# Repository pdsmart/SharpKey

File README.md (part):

## <font style="color: yellow;" size="6">The SharpKey</font>

<div style="text-align: justify">
The name SharpKey is derived from <b><u>Sharp</u></b> <b><u>Key</u></b>board Interface, as it is based on the original mz25key Sharp MZ-2500/MZ-2800 PS/2 Keyboard Interface.
<div style="padding-top: 0.8em;"></div>
The SharpKey Multi-HID Interface is a device which enables connection of Keyboards and Mice, via PS/2 or Bluetooth, to vintage Sharp and NEC computers. It is
housed in a small KM-24 black or light-grey casing to match the host console colour and takes up minimal additional space. It has two external ports, one for a PS/2 keyboard or mouse and the second
for a cable to connect with the host keyboard or mouse input socket. If bluetooth is used, the PS/2 port is not used and only a host cable from the host port is required.
<div style="padding-top: 0.8em;"></div>
In use the SharpKey takes power from the host, adding little extra overhead to the host computers power supply. It typically consumes a 30mA when active in interface mode rising to 150mA if the IoT web interface is enabled. Peak instantaneous startup current for WiFi can be 250mA.
</div>

<div style="padding-top: 0.8em;"></div>
<div style="text-align: justify">
This section describes the ports, interfaces, buttons and LEDs of the SharpKey.
<div style="padding-top: 0.8em;"></div>
</div>

#### <font style="color: yellow;" size="5">Ports</font>

<div style="text-align: justify">
The SharpKey is equipped with two mini-DIN female ports, an LED and a configuration switch for enabling the on-board WiFi IoT web interface and the Bluetooth device Pairing. The image
below shows the locations.
<div style="padding-top: 0.8em;"></div>
<div style="float: left;">

</div><br>
<div style="padding-top: 0.8em;"></div>
On the left is the HOST connector, this is an 8pin mini-DIN female socket into which a HOST specific cable is plugged. The cable interfaces the SharpKey to either a mouse or keyboard port
on a particular host, ie. Sharp MZ-2800.<br>
<div style="padding-top: 0.8em;"></div>
On the right is the PS/2 connector, this is a 6pin mini-DIN female socket into which a PS/2 keyboard or PS/2 mouse is plugged. This socket is hot-swappable so it is possible to unplug a 
device and re-insert it whilst the interface is powered on. Plugging a different device of the same type is possible but changing from a keyboard to a mouse/vis-a-viz is not possible as it
would require the HOST cable to be changed as well (ie. if the HOST side is connected to the keyboard input of a Sharp X68000 and the PS2 side to a PS/2 Keyboard, you would need to change the HOST
side to a X68000 mouse cable if you wanted to connect a PS/2 Mouse).
<div style="padding-top: 0.8em;"></div>
</div>

<div style='content: ""; clear: both; display: table;'>
    <div style='width: 26%; padding: 5px; padding-left: 1em; float: left'>
        
    </div>
    <div style='width: 25%; padding: 5px; padding-left: 1em; float: left'>
        
    </div>
</div>

<div style="padding-top: 0.8em;"></div>
<div style="text-align: justify">
Internally, there is an 8pin 2mm header connector, this is used when OTA Firmware upgrade fails (ie. bricked) or for development and debugging of new features. See the technical documentation for
more information on this connector and its use.
</div>
<div style="padding-top: 0.8em;"></div>
<div>
    
</div>

#### <font style="color: yellow;" size="5">LEDs</font>

<div style="text-align: justify">
The Blue Activity LED is used to indicate device operation and warn of errors or device status.
<div style="padding-top: 0.8em;"></div>
During normal operation, the Activity LED lights up for a second when the interface is powered on and then the LED powers off. If there is no PS/2 device connected, the LED will light permanently
until a PS/2 device is connected (or Bluetooth enabled and a device pairs with the SharpKey). During keyboard activity, the LED will pulse on each key press. During mouse activity, the LED will
only light up if the 'third wheel button' is pressed and the mouse enters configuration mode.
</div>
<div style="padding-top: 0.8em;"></div>

| LED State           | Occurrence       | Description                    |
| ---------           | -----------      | -----------                    |
| On                  | During power up  | Lights for 1 second then turns off. This indicates normal power up and initialisation successful. |
|                     | Normal use       | PS/2 Keyboard or mouse not connected, Bluetooth device not paired. |
| Off                 | During power up  | Device failure. |
|                     | Normal use       | Device running normally. |
| Pulsing             | Normal use       | LED lights briefly on each keyboard key pressed. |
|                     | WiFi Selection   | LED pulses 1 flash per 0.5 seconds when the WiFi key is being pressed for more than 2 seconds and the SharpKey indicates configured WiFi Client/Access Point mode selected. |
|                     |                  | LED Pulses 1 flash per 0.25 seconds when the WiFi key is being pressed for more than 5 seconds and the SharpKey indicates default parameter Access Point mode selected. |
|                     | Bluetooth Pairing| LED Pulses 1 flash per 0.125 seconds when the WiFi key is being pressed for more than 10 seconds and Bluetooth Pairing mode selected. |
|                     | NVS Reset        | LED Pulses 1 long flash per second when the WiFi key is being pressed for more than 15 seconds and NVS Reset is selected. |

#### <font style="color: yellow;" size="5">Switches</font>

<div style="text-align: justify">
The WiFi/Bluetooth configuration switch is located within the SharpKey casing and accessed via a pin-hole on the casing top, next to the LED. A non-conducting rod needs to be used, inserting
it into the pin-hole and depressing the internal switch.
<div style="padding-top: 0.8em;"></div>
The length of time the switch is depressed indicates the feature the user wishes to access. 
</div>
<div style="padding-top: 0.8em;"></div>

| Time Switch Depressed | LED | Feature |
| --------------------- | --- | ------- |
| 1 second              | Off.                 | Cancel any selected feature, ie. WiFi mode or Bluetooth pairing. |
| 2 key presses in 1 second | SharpKey reboots and LED will light until a key is pressed or mouse moved.                 | Reboot SharpKey. Used if you need to reboot the SharpKey, for example, changing from PS/2 to Bluetooth after disconnecting PS/2 device. |
| 2 - 4 seconds         | Flashes 2 times per second.                 | Select configured WiFi mode, Access Point or Client. |
| 5 - 9 seconds         | Flashes 4 times per second.                 | Select default parameter WiFi Access Point mode. |
| 10 - 14 seconds       | Flashes 8 times per second.                 | Select Bluetooth Pairing mode. |
| 15 - 19 seconds       | Flashes one long pulse per second.          | Select NVS Reset mode (clear all settings and restore to factory mode). |

See the relevant section for more information on accessing and using the different features.

#### <font style="color: yellow;" size="5">Cables</font>

<div style="text-align: justify">
Each host machine has different electrical and mechanical specifications for its keyboard and mouse inputs. The SharpKey is able to manage the electrical and protocol requirements but
the mechanical requirement must be met with a physical cable.
<div style="padding-top: 0.8em;"></div>
This means each host machine keyboard and mouse input port requires a unique cable from the SharpKey into the host keyboard or mouse port. On Sharp machines, the mouse port is common so
only one cable is required to connect the SharpKey to any Sharp mouse port. The different cables can be seen below.
<div style="padding-top: 0.8em;"></div>
</div>

<div style='content: ""; clear: both; display: table;'>
    <div style='width: 40%; padding: 5px; padding-left: 1em; float: left'>
        
    </div>
    <div style='width: 34%; padding: 5px; padding-left: 1em; float: left'>
        
    </div>
</div>
<div style='content: ""; clear: both; display: table;'>
    <div style='width: 23.33%; padding: 5px; padding-left: 1em; float: left'>
        
    </div>
    <div style='width: 33.33%; padding: 5px; padding-left: 1em; float: left'>
        
    </div>
    <div style='width: 33.33%; padding: 5px; padding-left: 1em; float: left'>
        
    </div>
</div>

<div style="text-align: justify">
Each cable has an 8pin mini-DIN connector attached (the MZ-2500 has 2 so either side connector can be used) which plugs into the SharpKey. The opposite end of the cable plugs into the host keyboard or mouse
port.
</div>

#### <font style="color: yellow;" size="5">Connecting the SharpKey</font>

<div style="text-align: justify">
Connecting the SharpKey is simply a matter of obtaining the correct cable for your host machine, either keyboard or mouse, plugging the 8pin mini-din end into the SharpKey and the opposite
end into your host machine keyboard or mouse port. 
<div style="padding-top: 0.8em;"></div>
If you intend to use a PS/2 Keyboard or PS/2 mouse, insert the keyboard/mouse 6pin mini-din connector into the opposite end of the SharpKey. If you are intending to use Bluetooth then no
connection needs to be made with the PS/2 port on the SharpKey.
<div style="padding-top: 0.1em;"></div>
<p style="line-height: 1.2;"><font style="color: silver;" size="4">NB. Bluetooth will only be enabled when no PS/2 device is connected.</font></p>
<div style="padding-top: 0.1em;"></div>
Once the cables have been connected, power on your machine and use the PS/2 keyboard/mouse or Bluetooth keyboard/mouse as normal. If any keyboard keys do no map correctly to the host
keys, you can use the IoT web interface to add key mappings as required.
<div style="padding-top: 0.1em;"></div>
<p style="line-height: 1.2;"><font style="color: silver;" size="4">NB. Bluetooth devices require pairing and once paired, on power up, may take a few seconds to connect. When using Bluetooth at power up, wake the bluetooth devices up by repeatedly hitting the shift key or shaking
the mouse, this is necessary as the device will be in sleep mode and the SharpKey wont be able to connect.</font></p>
</div>

#### <font style="color: yellow;" size="5">Bluetooth Pairing</font>

<div style="text-align: justify">
In addition to PS/2 HID devices, Bluetooth wireless devices can also be connected to the SharpKey.
<div style="padding-top: 0.8em;"></div>
In order to use Bluetooth, <u>No</u> PS/2 device should be connected to the SharpKey. If the SharpKey detects a PS/2 device during startup it will not enable Bluetooth.  The Bluetooth transceiver in the ESP32 is
not so powerful so your device needs to be in a 1m range or less (some devices, typically mice, operate over a much longer distance). 
<div style="padding-top: 0.8em;"></div>
On receipt, in <i>factory default mode</i> or after an <i>NVS Clear</i> function, the SharpKey will perform a Bluetooth scan looking for nearby devices which are in Pair mode. Simply press the <i>pairing</i> button on your keyboard or mouse device and within 5-10 seconds it should connect
without requiring a pairing PIN.
<div style="padding-top: 0.8em;"></div>
Upto 5 additional devices can be paired with the SharpKey (which will operate simultaneously if all 5 devices are connected) can be added by placing the SharpKey into <i>Pairing Mode</i>. To enter <i>Pairing Mode</i> press the Wifi/Config Enable switch for 10-15 seconds, as you hold the key
you will notice the Blue LED change pattern:
<ul style="line-height: 0.6em;"><font size="3">
<li>2-5 seconds it will flash twice per second which indicates <i>WiFi Enable Mode</i> is selected if you release the switch.</li>
<li>5-10 seconds it will flash 4 time per second indicating <i>Default WiFi Mode</i> is selected if you release the switch.</li>
<li>10-15 seconds it will flash 8 times per second indicating <i>Bluetooth Pairing Mode</i> selected if you release the switch.</li>
</font></ul>

Release the switch after 10 seconds and the SharpKey will enter pairing mode and connect with any HID devices it finds in Pairing mode. The SharpKey stays in 
pairing mode for 60 seconds during which time it will pair with as many HID devices it finds.
<div style="padding-top: 0.8em;"></div>
Device authentication (PIN entry) has been programmatically disabled for the SharpKey as it has no means to display a pairing PIN. This method generally works well for most BLE and BT Classic devices
but should your device require a PIN which cannot be disabled, after about 10 seconds the Blue LED will start flashing with 3 long pulses, repeated every second. If you see the LED flashing then enter the PIN code '<u>1234</u>' on your keyboard and press ENTER. If the LED continues
to flash, repeat the PIN entry until it pairs and the LED stops flashing.
<div style="padding-top: 0.8em;"></div>
On future power cycles of the SharpKey it will be necessary to shake or wake your bluetooth device so that it reconnects. This can be achieved by pressing the <i>Shift</i> key repeatedly on your keyboard or moving your mouse. If the bluetooth devices isnt woken, the SharpKey wont be able to see
it and connect. It can take 1-10 seconds to reconnect depending on your device and range from the SharpKey (the further the distance the longer it may take due to the ESP32 Bluetooth transceiver not being very powerful).
</div>

#### <font style="color: yellow;" size="5">Accessing the IoT Web Interface</font>

<div style="text-align: justify">
The SharpKey has several preconfigured keyboard maps, factory default set to a UK keyboard layout on all of the supported host machines. Using hotkeys (see below) it is possible to select a different map.
<div style="padding-top: 0.8em;"></div>
The in-built maps will evolve over time to support more keyboards and these updates will be distributed as a firmware update. Keyboards layouts currently supported are:
<ul style="line-height: 0.6em;"><font size="3">
  <li>Wyse KB-3926 UK Layout</li>
  <li>Generic OADG109 Japanese Layout</li>
  <li>Sanwa SKB-L1 Japanese Layout</li>
  <li>Perixx Periboard 810 UK Layout</li>
  <li>OMOTON K8508 UK Layout</li>
</font></ul>

There exists however an edge case of a key not working or not working the way it should for
an individual user, also other users may find their regional (country) keyboards not working well and these shortcomings needs to be addressed by the user who has more hands on experience.
To this end, the SharpKey can be configured to map any PS/2 code or code combinations into a key sequence expected by the active host. Bluetooth scancodes are internally mapped to PS/2 scancodes 
so all keyboard type (PS/2 or Bluetooth) mapping is performed using PS/2 codes.
<div style="padding-top: 0.8em;"></div>
In order to make changes the SharpKey is equipped with an in-built web server using WiFi technology and can be configured in Access Point mode (you connect your WiFi device to the SharpKey) or Client mode
where the SharpKey uses stored credentials to connect with your home network router.
<div style="padding-top: 0.8em;"></div>
To access the web interface, the SharpKey needs to enable the wifi Access Point or Client transceiver. This is done via the <a href="/sharpkey-usermanual/#switches">WiFi/BT Config switch</a>.
<div style="padding-top: 0.8em;"></div>
There are two WiFi modes, Access Point and Client:
<ul>
<li>Access Point is where the SharpKey acts as a WiFi router and you search via your computer/phone wifi settings for the WiFi network:
<font style="color: Tan;">sharpkey</font> and connect using the password: <font style="color: Tan;">sharpkey</font>. The SSID and password can be changed in the configuration but should you forget your changes, pressing the  WiFi/BT switch for more than 5 seconds
will force the SharpKey to enter Access Point mode using the aforementioned defaults.</li>
<li>Client mode is where the SharpKey connects to your home network, details of which must be pre-entered into the SharpKey via the Access Point mode. Once set, each time the SharpKey enters WiFi mode
it will automatically try to connect to your router, using DHCP (your router allocates it an address) or with a fixed address you provide.</li>
</ul>

The steps for accessing each of the modes can be seen in the table below.
<div style="padding-top: 0.8em;"></div>
</div>

| Mode                        | How to Access | Description                                |
| ----                        | ------------- | -----------                                |
| Access Point mode.<br>Initial setup or by forcing default mode. | Initial factory setup, pressing the WiFi switch for 5-10 seconds will enter WiFi Access Point mode. If a bad configuration has been made or you have a network change, press the WiFi switch for 5-10 seconds to load default parameters and enter Access Point mode. | Search on your computer or phone WiFi settings menu for the network:<font style="color: Tan;">sharpkey</font>. Connect with this network and enter the password:<font style="color: Tan;">sharpkey</font>. After successful connection, open a web browser and enter in the address bar: http://192.168.4.1 - you will now be able to access the SharpKey and configure the WiFi via <font style="color: Tan;">WiFi Manager</font>.|
| Access Point mode.          | Once the SharpKey has been configured and you selected AP Mode in the WiFi Manager, pressing the WiFi switch for 2-5 seconds will enter Access Point mode. | This mode is where you have selected Access Point mode via the WiFi Manager menu in the browser configuration. You can change the network name (SSID), password and IP address range to suit your requirements. In this mode you will always connect to the SharpKey by joining its network in the WiFi settings menu of your computer or phone and access the configuration web page using the settings you provided. |
| Client (also called Station) mode. | Once the SharpKey has been configured and you selected Client Mode in the WiFi Manager, pressing the WiFi switch for 2-5 seconds will enter Client mode. | This mode allows the SharpKey to connect with your network via WiFi login to your router. During the initial connection in Access Point mode, under the WiFi Manager menu, select and setup Client mode with your router credentials. Once configured, everytime you enable WiFi the SharpKey will connect to your router and be accessible by an allocated IP address on your network or a fixed IP address you entered in the WiFi Manager menu. |

<div style="text-align: justify">
After pressing the WiFi configuration switch for the required amount of time the device will reboot and enter the requested WiFi mode. The blue led will light and if it remains lit then an error has occurred. If it briefly flashes several times then the desired WiFi configuration has been setup and established.
<div style="padding-top: 0.8em;"></div>
If all is successful and you have either joined the Access Point network or the SharpKey has connected to your network, opening a browser and entering the correct IP address, (ie. http://192.168.4.1 for the initial Access Point mode) will see the status screen below.
The correct IP address is the one you configured in WiFi Manager, or in the case of Client Mode with DHCP enabled, the one allocated by your router which you can find by looking at the admin page of your router.
<div style="padding-top: 0.8em;"></div>
A visual indication of the SharpKey connecting to your
</div>

<div style="padding-top: 0.8em;"></div>

#### <font style="color: yellow;" size="5">Configuring Access Point Mode</font>

<div style="text-align: justify">
The SharpKey factory state automatically starts in Access Point mode when WiFi is enabled. WiFi is enabled by pressing the WiFi/BT Config switch for 2-5 seconds. Once the device is configured, if the device cannot be accessed (for example, due to network change), pressing the WiFi/BT Config switch for 5-10 seconds will automatically enter Access Point mode with default parameters.
<div style="padding-top: 0.8em;"></div>
The default parameters in unconfigured Access Point mode are below.
</div>
<div style="padding-top: 0.8em;"></div>

| Parameter      | Value |
| ---------      | ----- |
| SSID (network name) | sharpkey |
| Password       | sharpkey |
| Access Point IP address | 192.168.4.1 |
| Router address | 192.168.4.1 |
| DHCP assigned IP range | 192.168.4.2 - 192.168.4.254 |

<div style="text-align: justify">
After setting the SharpKey into WiFi mode, access the WiFi menu of your computer or phone and select the <font style="color: Tan;">sharpkey</font> network. Enter the password <font style="color: Tan;">sharpkey</font>, your computer or phone will now join the SharpKey network and you can access it's web interface.
<div style="padding-top: 0.8em;"></div>
Enter the URL http://192.168.4.1 into a web browser and you will be presented with the status screen:
</div>

<div style="text-align: justify">
The status screen shows 2 panels, a <font style="color: Tan;">WiFi Configuration</font> panel which shows the active WiFi configuration being used by the SharpKey and a <font style="color: Tan;">Version Information</font> panel which shows the firmware modules installed along with their version number and the disk filesystem version. This information can be used
for feature verification or fault tracking/raising a support ticket and also to view versions to see if an update pack offers newer software or fixes.
<div style="padding-top: 0.8em;"></div>
In the left side of the screen, called the sidebar menu, are the possible options available to view or configure in the web interface. This document details each of the options in more detail further down.
<div style="padding-top: 0.8em;"></div>
Click on the <font style="color: Tan;">WiFi Manager</font> option in the left sidebar menu. This will start the WiFi Manager configuration screen which will appear like:
</div>

<div style="text-align: justify">
You now have a choice, configure the SharpKey as an Access Point or as a Client. Access Point means the SharpKey provides the WiFi network and your computer/phone needs to connect with it via the WiFi settings menu. Client mode means you enter details of your home network and the SharpKey will automatically connect to your home network and your computer or phone
will see it as a device on your network.

If you decide to use Access Point mode, you can leave it configured with the defaults, or change them with the <i>Configure WiFi</i> panel below.
</div>

<div style="text-align: justify">
The options for the Access Point mode in the <i>Configure WiFi</i> panel are:
</div>
<div style="padding-top: 0.8em;"></div>

| Option    | Description |
| ------    | ----------- |
| WiFi Mode | Select the type of mode required, in this instance click on <font style="color: Tan;">Access Point</font>. |
| SSID      | This is the network name you will see on your computer or phone when you go to the Wifi settings menu and scan for available networks. Either leave it as default or change to a meaningful name. |
| Password  | This is the password your computer or phone will request when you choose to join the network identified by SSID. |
| IP Address| This is the IP address range the SharpKey will use for its DHCP server which allocates any connecting clients requesting an address. This value should end with a .1 which is assigned to the SharpKey and the DHCP server will allocate addresses xxx.xxx.xxx.2 - 254 to a connecting client. |
| Netmask   | This is the network mask used for filtering and masking IP addresses. Unless you are network savvy, always set this address to 255.255.255.0. |
| Gateway   | This is the gateway a computer or phone needs to route network requests. This should be the same as IP Address as the SharpKey doesnt perform routing. |

<div style="text-align: justify">
Once you have entered the required settings, press on <font style="color: Wheat;">Save</font> and the data will be validated. If the data is correct, a message will be displayed in green advising you all is ok and to press Reboot. If the message is in red, take note of the error and correct accordingly, pressing <font style="color: Wheat;">Save</font> once the error has been fixed.
<div style="padding-top: 0.8em;"></div>
After a successful save, press reboot and the SharpKey will reboot,  immediately entering WiFi mode for data confirmation (ie. you dont need to press the WiFi/BT Config switch again). Just allow a few seconds and then join with the SharpKey network using your computer or phones WiFi settings menu. Once connected to the SharpKey network, open a browser and enter the IP Address you 
chose in the <i>Configure WiFi</i> panel and you will be immediately taken to the SharpKey status menu.
</div>

#### <font style="color: yellow;" size="5">Configuring Client Mode</font>

<div style="text-align: justify">
The SharpKey factory state automatically starts in Access Point mode when WiFi is enabled. Follow the Access Point mode configuration up until you see the SharpKey status screen and follow the instructions below.
</div>

<div style="text-align: justify">
Click on the 'WiFi Manager' option in the left sidebar menu. This will start the WiFi Manager configuration screen which will appear like:
</div>

<div style="text-align: justify">
You now have a choice, configure the SharpKey as an Access Point, in which case follow the <font style="color: Tan;">Configure Access Point Mode</font> instructions, or configure the SharpKey in Client Mode.
<div style="padding-top: 0.8em;"></div>
If you decide on Client Mode, click on the <font style="color: Tan;">Client</font> radio button and the <i>Configure WiFi</i> panel will update to request Client parameters. There are two distinct Client mode's of operation, either <font style="color: Tan;">DHCP Enabled</font> where the router provides all network connection information or <font style="color: Tan;">DHCP Disabled</font> where you manually specify network parameters.
<div style="padding-top: 0.8em;"></div>
The initial parameters requested in the <i>Configure WiFi</i> panel appear below, which is the same for DHCP Enabled or Disabled mode.
</div>
<div style="padding-top: 0.8em;"></div>

| Option    | Description |
| ------    | ----------- |
| WiFi Mode | Select the type of mode required, in this instance click on <font style="color: Tan;">Client</font>. |
| SSID      | This is the network name you want the SharpKey to join with in order to establish a connection with your home network. |
| Password  | This is the password the SharpKey will provide to your router to authenticate itself and establish a connection. |
| DHCP Mode | This specifies wether you want your router to provide all network information (Enabled) or you will manually provide it (Disabled). |

The panel will appear as indicated below:

<div style="text-align: justify">
Should you decide to use DHCP Disabled mode, additional parameters are requested in the <i>Configure WiFi</i> panel:
</div>
<div style="padding-top: 0.8em;"></div>

| Option    | Description |
| ------    | ----------- |
| IP Address| This is the address the SharpKey will use for itself on your home network. You will connect to the SharpKey using this address in your browser, ie. http://&lt;IP Address&gt;. |
| Netmask   | This is the filter and masking parameter in order for your SharpKey to occupy parts of a subnet. Unless your network savvy, enter 255.255.255.0 |
| Gateway   | This is the IP address of the device on your network which acts as a gateway to the internet/intranet. The SharpKey is not internet aware so enter the same value as the IP Address above. |

The updated panel will appear as indicated below:

<div style="text-align: justify">
Once you have set the correct mode of operation and entered the requested parameters press <font style="color: Wheat;">Save</font> and the parameters will be validated and updated. Should the parameters be valid a green success message will appear indicating this and requesting you to press reboot. Should the parameters be invalid, a red message will appear indicating which entry is incorrect, fix it and press <font style="color: Wheat;">Save</font> again.
<div style="padding-top: 0.8em;"></div>
After a successful save, press <font style="color: Wheat;">Reboot</font> on the left side-bar and the SharpKey will reboot. Press the WiFi switch again if you want to enter WiFi mode with the new settings. If the SharpKey fails to join with the network the LED will stay lit otherwise will blink several short pulses to confirm WiFi connection. If the SharpKey fails to enter WiFi mode (ie. cannot connect with your router), the LED will remain lit and after 1 minute
it will reboot. In this situation, press the WiFi/BT Config switch for 5-8 seconds and it will enter WiFi Access Point mode with default settings so you can reconfirm the credentials you entered.
</div>

#### <font style="color: yellow;" size="6">OTA Updates</font>

<div style="text-align: justify">
The SharpKey is equipped with a feature to allow updates to its internal firmware or disk filing system. The firmware or filesystem can be upgraded for newer features or to fix known bugs. 
<div style="padding-top: 0.8em;"></div>
In order to use the OTA Updates feature, access the web interface using the Access Point/Client information above and open a browser to load the initial status page, ie:
</div>

<div style="text-align: justify">
Click on the <font style="color: Tan;">OTA Update</font> option in the left sidebar menu. This will start the OTA Update configuration screen which will appear like:
</div>

<div style="text-align: justify">
The OTA Update screen shows 4 panels:
   
<ul>
 <li>a <font style="color: Tan;">Version Information</font> panel which shows the firmware modules installed along with their version number and the disk filesystem version. This information can be used
for feature verification or fault tracking/raising a support ticket and also to view versions to see if an update pack offers newer software or fixes.</li>
<li>an <font style="color: Tan;">ESP32 Partitions</font> panel which shows the layout of the NVS Flash RAM on the ESP32 SoC which powers the SharpKey. The information of interest is the Partion Names: ota_0, ota_1 and filesys. The SharpKey uses a fault tolerant update system in a round robin method. If the current firmware is running on partition ota_0 then any updates will be placed onto ota_1. After update, should
the SharpKey fail to boot an automatic rollback is performed and the SharpKey will reboot off ota_0. This is not the case for the filesystem <font style="color: Tan;">filesys</font>, if an update fails then the filesystem may be corrupted and the web interface will fail to work. In this case an external programming probe needs to be connected to the SharpKey in order to reflash the filesystem. This is a rare occurrence and
only happens due to software bugs or power outages.</li>
<li>a <font style="color: Tan;">Firmware Upload</font> panel which allows you to select a new firmware file and upload it into the SharpKey.</li>
<li>a <font style="color: Tan;">File Pack Upload</font> panel which allows you to select a new filesystem image file and upload it into the SharpKey.</li>
</ul>

In order to upgrade the firmware, click on the <font style="color: Wheat;">Select file</font> button in the <font style="color: Tan;">Firmware Upload</font> panel and choose a stored or downloaded firmware image. Validation will occur before programming so if you choose the wrong image, the SharpKey will refuse to update. Validation will also check the version and block the update if the version chosen is the same as the current firmware. Once selected, the panel will update as follows:
</div>

<div style="text-align: justify">
Click on the <font style="color: Wheat;">Upgrade</font> button if you are ready to upload and flash the new firmware into the SharpKey or click <font style="color: Wheat;">Cancel</font> to clear the chosen file. Once you press <font style="color: Wheat;">Upgrade</font> the update procedure will commence, firstly the file will be validated and if valid, file upload will take place and the panel will change showing the status:
</div>

<div style="text-align: justify">
After a successful upload, a green success message will appear advising you to perform a reboot operation. If a red message appears, reboot the SharpKey and try the firmware upload again. The failsafe mechanism will never overwrite the current firmware so you can always restart the SharpKey.
</div>

<div style="text-align: justify">
In order to upgrade the filepack (the filesystem which contains key mapping images and web server files), click on the <font style="color: Wheat;">Select file</font> button in the <font style="color: Tan;">File Pack Upload</font> panel and choose a stored or downloaded filepack image. Validation will occur before programming so if you choose the wrong image, the SharpKey will refuse to update. Once selected, the panel will update as follows:
</div>

<div style="text-align: justify">
Click on the <font style="color: Wheat;">Upgrade</font> button if you are ready to upload and flash the new filepack into the SharpKey or click <font style="color: Wheat;">Cancel</font> to clear the chosen file. Once you press Upgrade the update procedure will commence, firstly the file will be validated and if valid, file upload will take place and the panel will change showing the status:
</div>

<div style="text-align: justify">
After a successful upload, a green success message will appear advising you to perform a reboot operation.
<div style="padding-top: 0.8em;"></div>
If a red message appears, reboot the SharpKey and try the filepack upload again. In this situation, where a filepack update has failed, if the SharpKey fails to enter WiFi mode then there is a good chance the filesystem is corrupted. The SharpKey interface will continue
to operate but no access will be possible to the web interface. In order to correct this, an external programming probe needs to be connected to the SharpKey in order to reflash the filesystem. See the technical documentation on a correct procedure. The situation where a filepack upload fails and corruption occurs should be very rare, just ensure power is continuously applied
to the SharpKey during an upload.
</div>

## <font style="color: yellow;" size="6">Key Map Editor</font>

<div style="text-align: justify">
To cater for unmapped key combinations or keyboards with different layout, configuration and scan codes, the SharpKey allows keyboard map editting. The key maps can be updated via the in-built keymap editor or via a local file save-edit-upload procedure using a tool such as <font style="color: Tan;">dhex</font>. If the key mapping file becomes corrupted you can upload a backup from local file or
let the SharpKey reload from the internal default map so another attempt at key map editting can be made.
<div style="padding-top: 0.8em;"></div>
Given the differences between the various supported machines, the key map editor and it's data differ per model, so a section is dedicated to each machine below, describing the mapping logic and the editor use in making changes. The keymap can only be editted for the active host detected by the SharpKey on startup. If a host is not detected then no keymap editting option will 
appear in the left side bar menu.
<div style="padding-top: 0.8em;"></div>
The basic key map editor, common to all supported hosts, is based on a hex input table, with mapping priority top down, where each entry in the table specifies one key map. Data can be entered in hex or decimal values and some input fields have popover boxes which aid in choosing features such as SHIFT key to aid in the configuration process. 
<div style="padding-top: 0.8em;"></div>
To access the keymap editor of the active host, start the web interface using the Access Point/Client information above and open a browser to load the initial status page, an example of which is below.
</div>

<div style="text-align: justify">
Click on the <font style="color: Wheat;">&lt;HOST&gt; KeyMap</font> option in the left sidebar menu. This will start the key map editor screen for the active host which will be similar to the example below.
</div>

<div style="text-align: justify">
There are 2 panels in the keymap editor, one is for direct input and editting of the key map values, the second is for saving and loading of a keymap file to a local disk. The latter option can be used for backup or to allow external editting of the keymap using local computer tools.
<div style="padding-top: 0.8em;"></div>
In the <font style="color: Tan;">KeyMap Editor</font> panel, a table will be displayed, based on responsive technology which will auto size to the viewable window, use the mouse scroll wheel to scroll down or the TAB/Cursor keys to scroll left and right.
<div style="padding-top: 0.8em;"></div>
The table headers differ depending on the active host and will be described in more detail in the host sections below.
<div style="padding-top: 0.8em;"></div>
The editor can add, delete, swap, save changes or reload using the four buttons amd two columns on the right of the table as follows: 
<ul>
<li>to add a column, click the green + symbol and a blank line will appear on the row below the +. All values will be set to disabled and require completion to become active.</li>
<li>to delete a single row, click the red - symbol ON the row you wish to delete.</li>
<li>to delete multiple rows, click on the Tick Box to the right of each row to be deleted. When one or more tick boxes are ticked, the blue <font style="color: Wheat;">Delete</font> button will be made active, press <font style="color: Wheat;">Delete</font> and the rows will be removed.</li>
<li>to swap TWO rows, click the Tick Box to the right of each row, TWO rows only should be ticked. Once two rows have been ticked, the blue <font style="color: Wheat;">Swap</font> button will be made active, press <font style="color: Wheat;">Swap</font> and the rows will be swapped.</li>
<li>to save the keymap (make it active on next reboot), once you have made data changes the blue <font style="color: Wheat;">Save</font> button will be made active, click on it to save the changes.</li>
<li>once changes have been made, the blue <font style="color: Wheat;">Reload</font> button will be made active, clicking this button at any time will discard all changes and reload the keymap.</li>
</ul>

Messages will be displayed in the status box just above the buttons, this is where errors will be reported if any occur.
<div style="padding-top: 0.8em;"></div>
Please see the sections below for more specific keymap detail.
</div>

#### <font style="color: yellow;" size="5">Sharp MZ-2500 / MZ-2800 Key Map</font>

<div style="text-align: justify">
The MZ-2500 and MZ-2800 models share a common key map table. In common with other supported host machines, the key map allows targetting a map at a specific keyboard model (ie. Wyse KB-3296) and a specific host variant (ie. MZ-80B on an MZ-2500). 
<div style="padding-top: 0.8em;"></div>
The MZ-2500/MZ-2800 machines use a keyboard which is based on a 13x8 or 14x8 key matrix where all inactive keys see a logic <font style="color: Tan;">1</font> and an active key sees a logic <font style="color: Tan;">0</font>. The MZ-2500 keyboard matrix can be visualised in the following tables and image along with the keyboard layout. The first table has the column as the horizontal header and the second table has the row as the horizontal header.
</div>
        
        MZ-2500 Keyboard Map.
        
         Row     D7        D6        D5        D4        D3        D2        D1        D0
        ----------------------------------------------------------------------------------
          0      F8        F7        F6        F5        F4        F3        F2        F1
          1      KP -      KP +      KP .      KP ,      KP 9      KP 8      F1O       F9
          2      KP 7      KP 6      KP 5      KP 4      KP 3      KP 2      KP 1      KP 0
          3      BREAK     RIGHT     LEFT      DOWN      UP        RETURN    SPACE     TAB
          4       G         F         E        D         C         B         A         / ?
          5       O         N         M        L         K         J         I         H
          6       W         V         U        T         S         R         Q         P
          7       , <       . >       _        YEN |     ^ '¿      Z ¿       Y         X ¿ 
          8       7 '       6 &       5 %      4 $       3 #       2 "       1 !       0
          9                 [ {       @ `      - =       ; +       : *       9 )       8 (
         10       KP /      KP *      ESC      BACKSPACE INST/DEL  CLR/HOME  COPY      ] }
         11                                    CTRL      KANA      SHIFT     LOCK      GRAPH
         12                                                                  KJ2       KJ1 
         13                                                                  HELP      ARGO 
        
         Col      0        1         2         3         4         5         6         7        8        9        10       11       12      13
         --------------------------------------------------------------------------------------------------------------------------------------
         D0       F1       F9        KP 0      TAB       / ?       H         P         X        0        8 (      ] }      GRAPH    KJ1     ARGO
         D1       F2       F10       KP 1      SPACE     A         I         Q         Y        1 !      9 )      COPY     LOCK     KJ2     HELP
         D2       F3       KP 8      KP 2      RETURN    B         J         R         Z        2 "      : *      CLR/HOME SHIFT
         D3       F4       KP 9      KP 3      UP        C         K         S         ^ '¿     3 #      ; +      INST/DEL KANA
         D4       F5       KP ,      KP 4      DOWN      D         L         T         YEN |    4 $      - =      BACKSPACE CTRL
         D5       F6       KP .      KP 5      LEFT      E         M         U         _        5 %      @ `      ESC
         D6       F7       KP +      KP 6      RIGHT     F         N         V         . >      6 &      [ {      KP *
         D7       F8       KP -      KP 7      BREAK     G         O         W         , <      7 '               KP /

<div style="text-align: justify">
The MZ-2800 keyboard matrix can be visualised in the following images, the first image is the keyboard layout and the second is the keyboard matrix.
</div>

<div style="text-align: justify">
A PS/2 key (Bluetooth keyboards are internally mapped to PS/2 keys) may require activation of one or more row/column pairs within the keyboard matrix AND possibly deactivation of another row/column pair. To cater for this, 14 parameters are
provided per single key map, all of which need to be configured or defaulted, which is described below.
<div style="padding-top: 0.8em;"></div>
The mapping process traverses the mapping table from top to bottom everytime a PS/2 key is pressed and if a key is matched, the MZ-2500/2800 output matrix is updated using a <font style="color: Tan;">Make Row</font> parameter which points to a row in the matrix and a <font style="color: Tan;">Make Key</font> parameter which sets, via logical OR, the 8 bit column data for that row. 
Upto 3 matrix bits can be set (3 key presses on the MZ-2500/2800 keyboard) per PS/2 key. Upto 2 matrix releases can be set per PS/2 key. A key release is used when a modifier may already have been pressed, ie. SHIFT and it needs to be released to set the required key into the matrix. Both set and releases use logic <font style="color: Tan;">1</font> to indicate an active state.
<div style="padding-top: 0.2em;"></div>
<p style="margin-left:2%; margin-right: 1%;"><font size="4">ie. Make Row 1 = 0x01, Make Key 1 = 0x80 - Using the MZ-2500 matrix map below, this combination would see the KeyPad Minus key being pressed on the output matrix which is sent to the MZ-2500 as keyboard input, the MZ-2500 would then react by detecting and acting on a KeyPad Minus key being pressed.</font></p>
<div style="padding-top: 0.2em;"></div>
In the mapping table, for the matrix Row and Key values, a set bit = 1 and a reset bit = 0 which is the inverse of the actual MZ-2500/MZ-2800 keyboard matrix state but makes understanding and configuration easier. If the Row is set to 255 (0xFF), which is a marker value indicating an unused parameter, then that particular entry is ignored. 
<div style="padding-top: 0.8em;"></div>
The following table describes each configurable parameter forming a single key map.
</div>
<div style="padding-top: 0.8em;"></div>

| Parameter        | Description |
| ---------        | ----------- |
| PS/2 KeyCode     | This is the raw PS/2 Keyboard Code for any given key excluding E0/E1 or Break modifiers which are reflected in the PS/2 Control Key flag. |
| PS/2 Control Key | This is the control keys to be matched for any given PS/2 KeyCode. They include SHIFT, CTRL, CAPS, ALT, ALTGR, GUI, FUNC and BREAK (not break key but key break or release). |
| For Keyboard     | This is a flag to specify a particular PS/2 or Bluetooth keyboard model(s) to which this map will be active if the connected keyboard matches. |                                                              
| For Host Model   | This is a flag to specify a model or set of models the key map is active for. The MZ-2500 can emulate an MZ-80B, MZ-2000 and MZ-2500 and the MZ-2800 can emulate an MZ-2500 or MZ-2800. |                                                            
| Make Row 1       | This is the row in the MZ-2500/MZ-2800 keyboard matrix to activate when the defined PS/2 KeyCode matches. |                                                           
| Make Key 1       | This is the column in the MZ-2500/MZ-2800 keyboard matrix which will be activated for a matching PS/2 KeyCode. |                                                           
| Make Row 2       | Same as Make Row 1, second row activation if required. 0xFF = disabled. |                                                          
| Make Key 2       | Same as Make Key 1.            |                                             
| Make Row 3       | Same as Make Row 1, third row activation if required. 0xFF = disabled. |                                                        
| Make Key 3       | Same as Make Key 1.           |                                            
| Break Row 1      | This is the row in the MZ-2500/MZ-2800 keyboard matrix to be de-activated, if set, when the defined PS/2 KeyCode matches. |
| Break Key 1      | This is the column in the MZ-2500/MZ-2800 keyboard matrix which will be de-activated when PS/2 KeyCode matches. |
| Break Row 2      | Same as Break Row 1, second row to be de-activeted if required. oxFF = disabled. |
| Break Key 2      | Same as Break Key 1.   |

<div style="text-align: justify">
All the keymap parameters are shown in the key map editor using HEX notation, ie:
</div>

<div style="text-align: justify">
All the keymap rows are stored in the table and the viewable table size is set according to the browser and/or computer screen size. To view hidden rows, use the mouse scroll wheel.
<div style="padding-top: 0.8em;"></div>
Data entry can be made in HEX or DECIMAL notation by clicking on a column and entering a value, then click on the next column and enter a value repeating, or click once then use the TAB key for more rapid data entry. Detail for each column
and it's reqired input values can be seen below.
<div style="padding-top: 0.8em;"></div>
<font style="color: cyan;">PS/2 KeyCode</font> - This column expects a PS/2 or Bluetooth keyboard scancode which can be found in your keyboard user manual or on the web where there are many references.
ie. the key <font style="color: Tan;">A</font> has a generic scancode value of 0x1C. HEX codes are not that user friendly and as there are many keyboards with many differing scancodes it is not possible to offer a picklist.
<div style="padding-top: 0.8em;"></div>
PS/2 scancodes can be represented by multiple bytes, only use the primary byte and ignore extended code seqeuences such as E0/E1/F0 as these are internally processed and the corresponding feature selected in the <font style="color: Tan;">PS/2 Control Key</font> column.
<div style="padding-top: 0.8em;"></div>
<font style="color: cyan;">PS/2 Control Key</font> - This parameter indicates which modifier keys (ie. CTRL, SHIFT etc) are pressed along with the PS/2 scancode in order to make a match. As a hex value is required, the modifier values are as follows:
</div>
<div style="font-size: 20px; border-collapse: collapse; table-layout: fixed; border: 3px;margin: 0;padding:0.2em;">
<table>
<tr>
  <th>Modifier Key</th><th>Value</th> <th>Modifier Key</th><th>Value</th> <th>Modifier Key</th><th>Value</th> <th>Modifier Key</th><th>Value</th>
</tr>
<tr>
  <td>SHIFT</td><td>0x01</td><td>CTRL</td><td>0x02</td><td>CAPS</td><td>0x04</td><td>ALT</td><td>0x08</td>
</tr>
<tr>
  <td>ALTGR</td><td>0x10</td><td>GUI</td><td>0x20</td><td>FUNC</td><td>0x40</td><td>BREAK</td><td>0x80</td>
</tr>
</table>
</div>
<div style="text-align: justify">
A popover picklist has been added to this field, when you click in the field (tabbing into the field wont show the popover) a popover will appear, example below. Click on the key modifiers you require to be matched along with the PS/2 scancode in order for the map to make a match and process the rest of the mapping parameters.
</div>

<div style="text-align: justify">
<font style="color: cyan;">For Keyboard</font> - This column expects an 8bit value, each bit indicates a supported keyboard model and if the active keyboard matches one of the set bits the rest of the mapping parameters will be processed. 
<div style="padding-top: 0.8em;"></div>
Valid values are in the table below with five keyboard models defined and the rest are place markers ready for assigning to a custom keyboard. ie. your own keyboard mappings could be assigned to <font style="color: Tan;">Keyboard 4</font> and using the hotkey SHIFT+CTRL+ESC+KeyPad_4 will set the active keyboard to <font style="color: Tan;">Keyboard 4</font> and your mappings will then be active. 
<div style="padding-top: 0.8em;"></div>
A value of 255 (0xFF) in this field enables the keymap for all keyboard models. Most of the default mappings are enabled for all keyboards, placing your own mapping higher up in the mapping table makes it take priority over the standard map.
</div>
<div style="padding-top: 0.8em;"></div>
<div style="font-size: 20px; border-collapse: collapse; table-layout: fixed; border: 3px;margin: 0;padding:0.2em;">
<table>
<tr>
  <th>Keyboard Model</th><th>Value</th> <th>Keyboard Model</th><th>Value</th> <th>Keyboard Model</th><th>Value</th> <th>Keyboard Model</th><th>Value</th>
</tr>
<tr>
  <td>UK WYSE KB3926</td><td>0x01</td><td>JAPAN OADG109</td><td>0x02</td><td>JAPAN Sanwa SKB-L1</td><td>0x04</td><td>Keyboard 4</td><td>0x08</td>
</tr>
<tr>
  <td>Keyboard 5</td><td>0x10</td><td>Keyboard 6</td><td>0x20</td><td>UK Periboard 810 (BT)</td><td>0x40</td><td>UK OMOTON K8508 (BT)</td><td>0x80</td>
</tr>
</table>
</div>
<div style="text-align: justify">
A popover picklist has been added to this field, when you click in the field (tabbing into the field wont show the popover) a popover will appear, example below. Click on the keyboard models and your mapping will be enabled for the indicated keyboard models or use ALL for all keyboards.
</div>

<div style="text-align: justify">
<font style="color: cyan;">For Host Model</font> - This column expects an 8bit value, each bit indicating a machine model the map will be active with. The MZ-2500 is capable of running as an MZ-80B, MZ-2000 and MZ-2550 with each having slightly different key mappings and the MZ-2800 also has differences so this field is used to target a key 
map at a particular machine or set of machines.
<div style="padding-top: 0.8em;"></div>
Valid values are in the table below with a value of 255 (0xFF) indicating all host models.
</div>

<div style="padding-top: 0.8em;"></div>
<div style="font-size: 20px; border-collapse: collapse; table-layout: fixed; border: 3px;margin: 0;padding:0.2em;">
<table>
<tr>
  <th>Host Model</th><th>Value</th> <th>Host Model</th><th>Value</th> <th>Host Model</th><th>Value</th> <th>KHost Model</th><th>Value</th>
</tr>
<tr>
  <td>MZ80B</td><td>0x01</td><td>MZ2000</td><td>0x02</td><td>MZ2500</td><td>0x04</td><td>MZ2800</td><td>0x08</td>
</tr>
</table>
</div>

<div style="text-align: justify">
A popover picklist has been added to this field, when you click in the field (tabbing into the field wont show the popover) a popover will appear, example below. Click on the Host Model and your mapping will be enabled for the indicated models or use ALL for all possible hosts.
</div>

<div style="text-align: justify">
<font style="color: cyan;">Make Row 1, Row 2, Row 3, Break Row 1, Row 2</font> - This column expects an 4bit value representing a strobe row from 0 to 15. A value of 255 (0xFF) indicates the parameter is not used. Select the row to target in the output matrix when you need to activate/deactivate a key that the host will see.
</div>
<div style="padding-top: 0.8em;"></div>
<div style="text-align: justify">
A popover select list has been added to this field, when you click in the field (tabbing into the field wont show the popover) a popover will appear, example below. Click on Strobe Row you wish to select, the strobe rows and columns appear in the keyboard matrix outlined in the MZ-2500/MZ-2800 documentation or use the MZ-2500 keyboard table above.
</div>

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
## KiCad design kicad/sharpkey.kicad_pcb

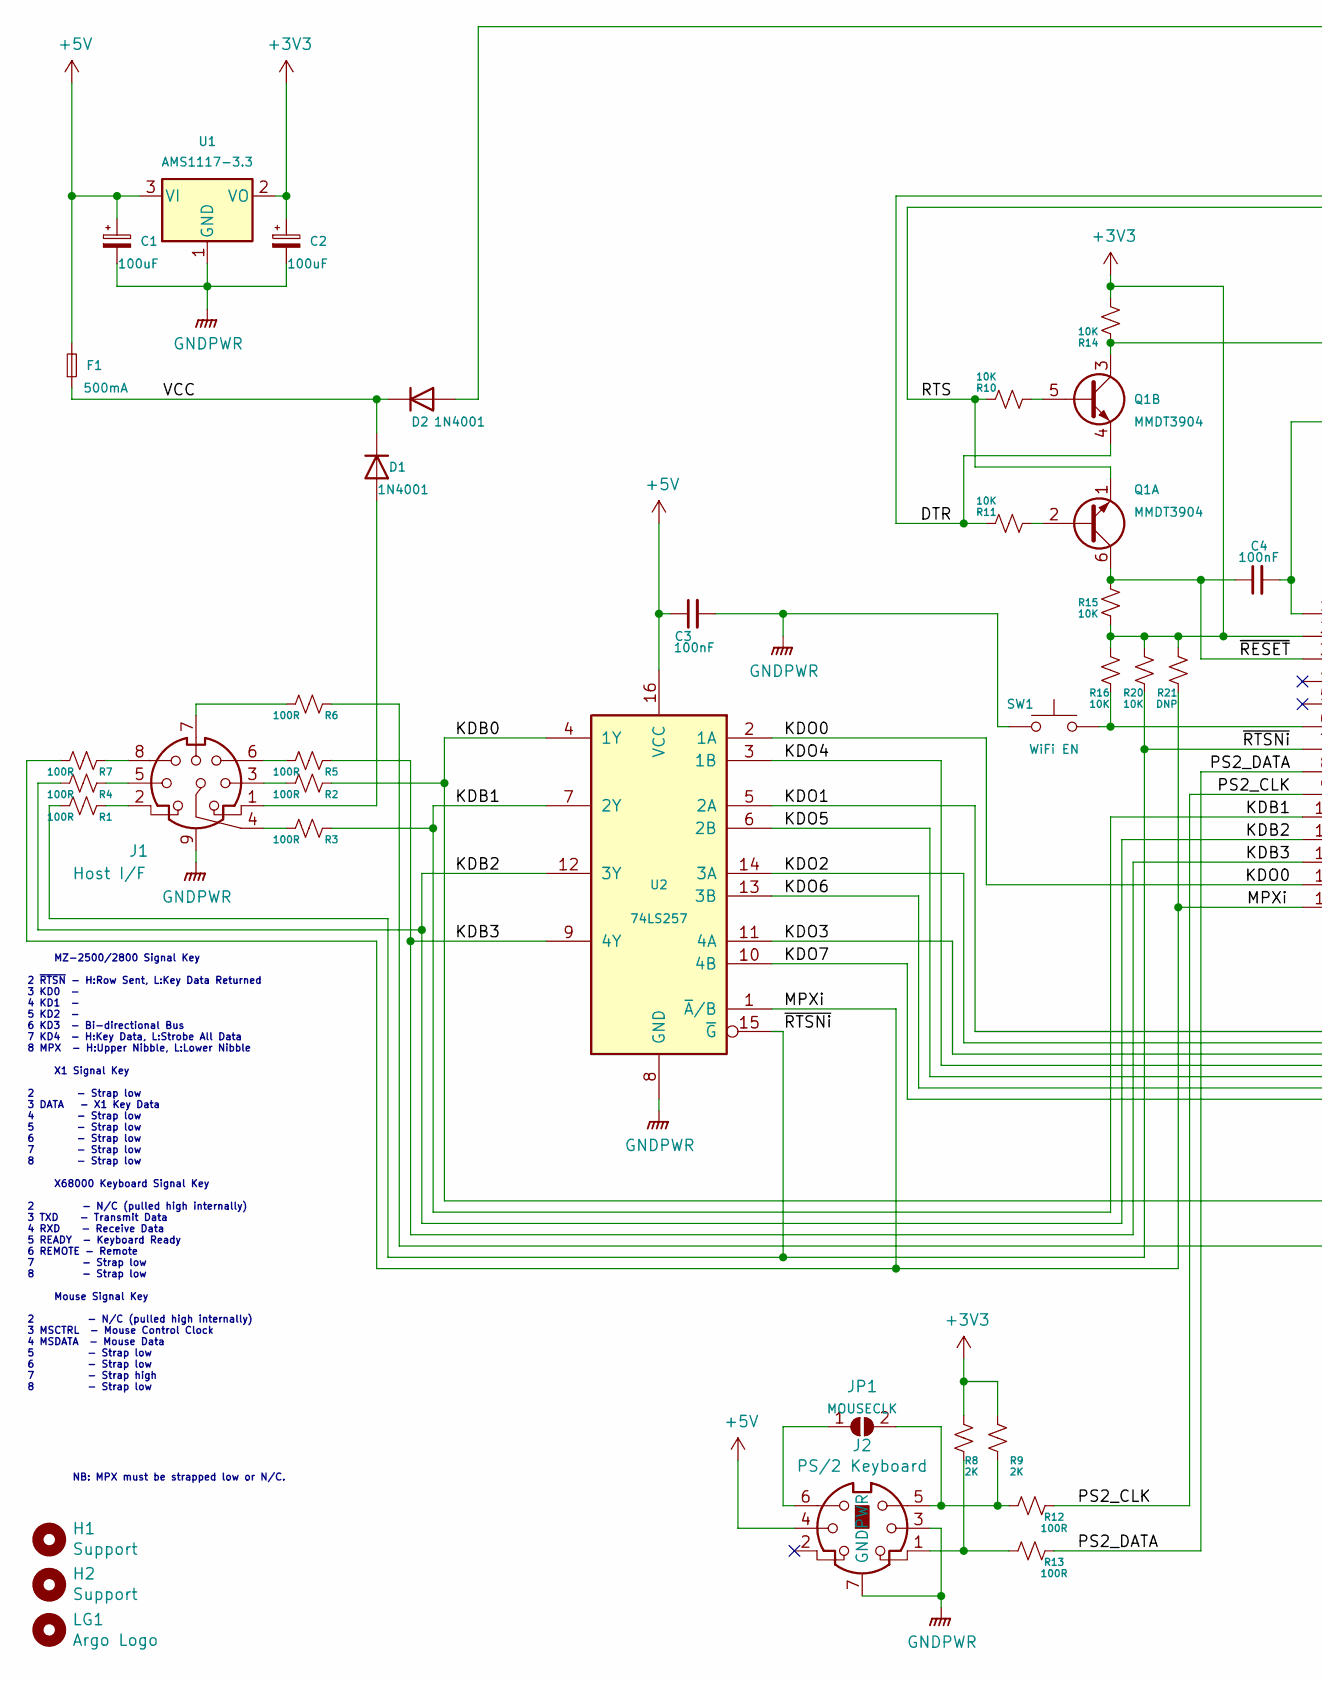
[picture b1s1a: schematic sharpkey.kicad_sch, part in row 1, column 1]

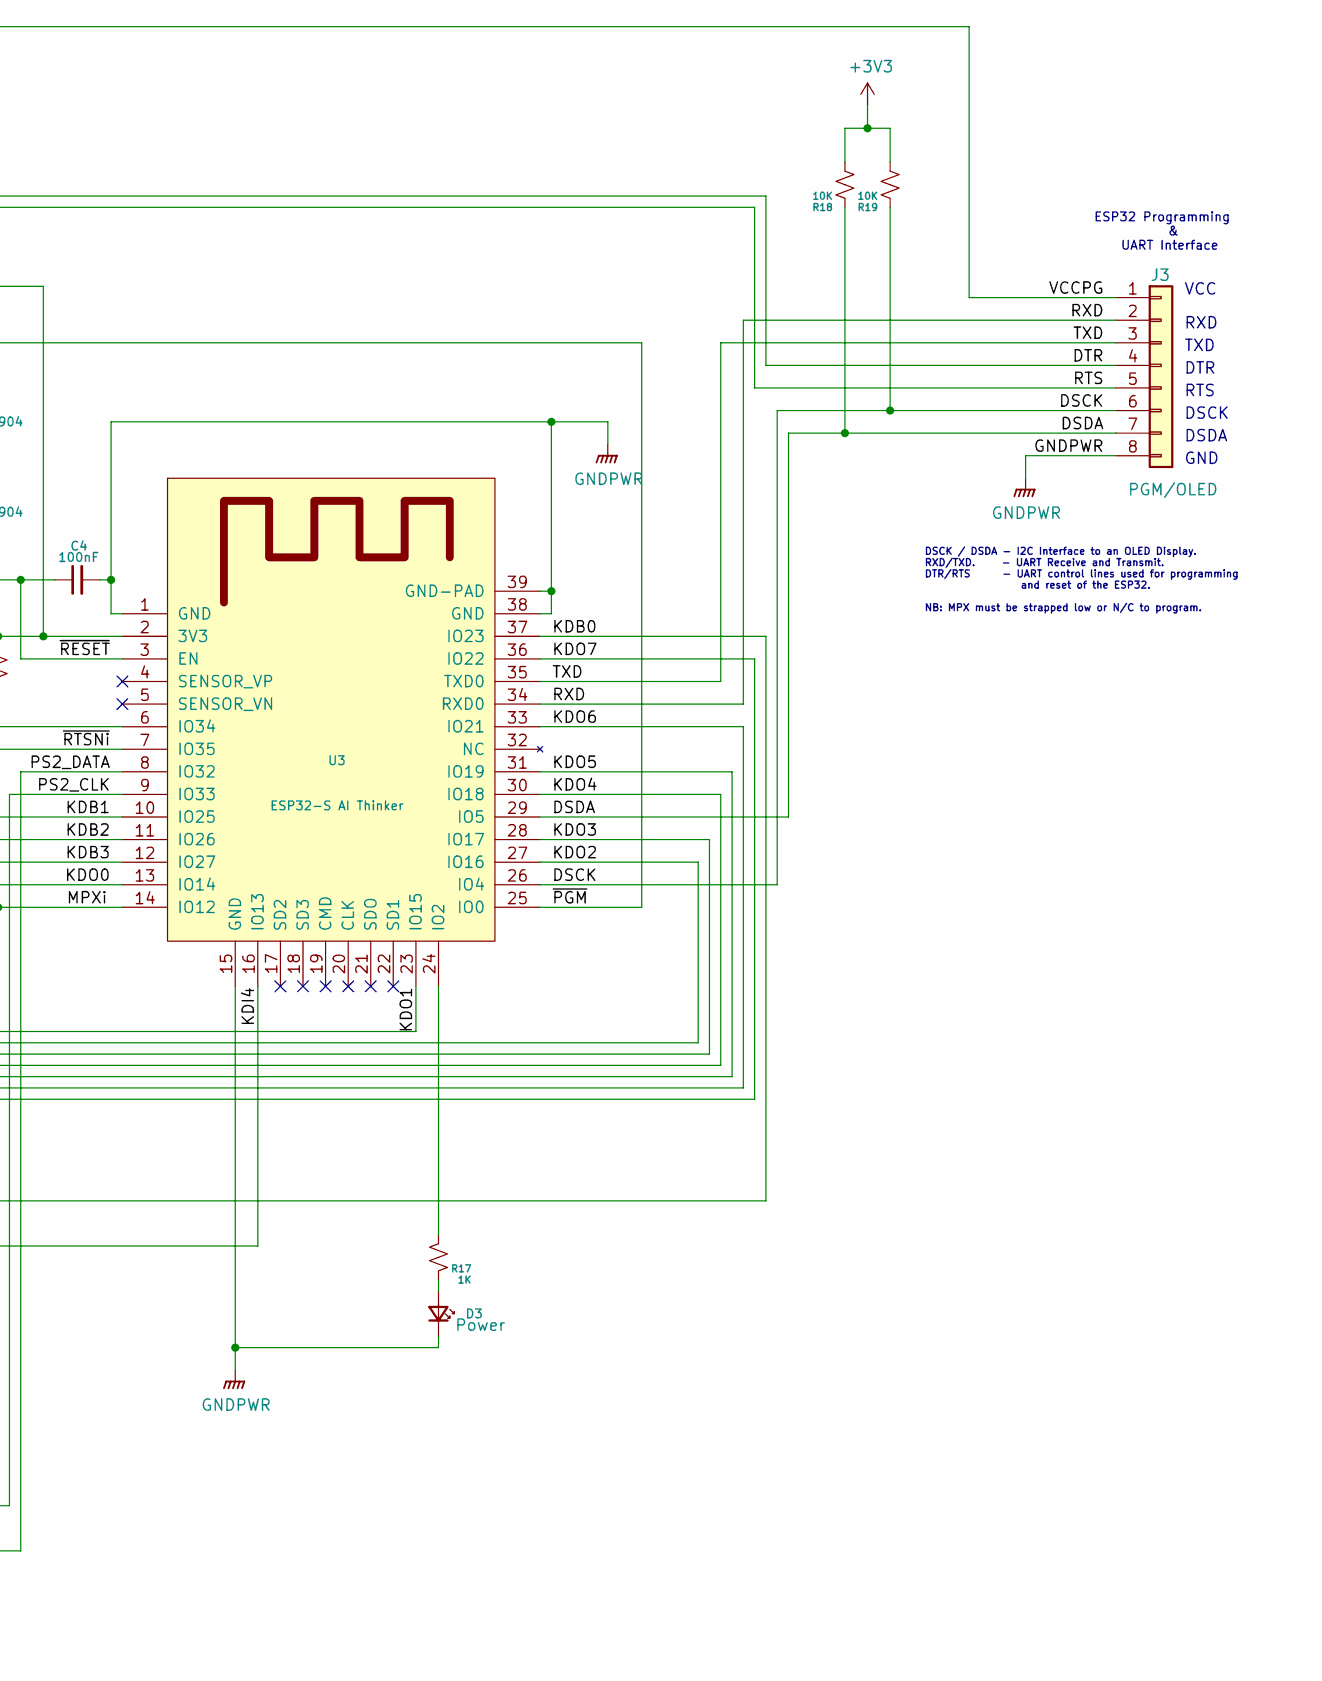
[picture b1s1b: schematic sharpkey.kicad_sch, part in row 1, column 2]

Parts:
C1, C2: 100uF; C_1210_3225Metric_Pad1.42x2.65mm_HandSolder
C3, C4: 100nF; C_0805_2012Metric
D1, D2: 1N4001; D_1206_3216Metric
D3: Power; LED_D3.0mm_Clear
F1: 500mA; Fuse_1806_4516Metric
H1, H2: Support; MountingHole_2.1mm
J1: Host I/F; Mini_din8_ps2
J2: PS/2 Keyboard; Mini_din6_ps2
J3: PGM/OLED; PinHeader_1x08_P2.00mm_Vertical
JP1: MOUSECLK; SolderJumper-2_P1.3mm_Open_Pad1.0x1.5mm
LG1: Argo Logo; Argo
Q1: MMDT3904; SOT-363_SC-70-6
R1, R2, R3, R4, R5, R6, R7, R12, R13: 100R; R_0805_2012Metric
R8, R9: 2K; R_0805_2012Metric
R10, R11, R14, R15, R16, R18, R19, R20: 10K; R_0805_2012Metric
R17: 1K; R_0805_2012Metric
R21: DNP; R_0805_2012Metric
SW1: WiFi EN; SW_SPST_B3S-1000
U1: AMS1117-3.3; SOT-223-3_TabPin2
U2: 74LS257; SOIC-16_3.9x9.9mm_P1.27mm
U3: ESP32-S AI Thinker; ESP32-S

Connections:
+3V3: C2.1, R8.1, R9.1, R14.2, R15.1, R16.2, R18.2, R19.2, R20.2, R21.2, U1.2 (VO), U3.2 (3V3)
+5V: C1.1, C3.1, F1.2, J2.4, U1.3 (VI), U2.16 (VCC)
/DSCK: J3.6, R19.1, U3.26 (IO4)
/DSDA: J3.7, R18.1, U3.29 (IO5)
/DTR: J3.4, Q1.4 (E2), R11.2
/KDB0: R2.2, U2.4 (1Y), U3.37 (IO23)
/KDB1: R3.2, U2.7 (2Y), U3.10 (IO25)
/KDB2: R4.1, U2.12 (3Y), U3.11 (IO26)
/KDB3: R5.2, U2.9 (4Y), U3.12 (IO27)
/KDI4: R6.2, U3.16 (IO13)
/KDO0: U2.2 (1A), U3.13 (IO14)
/KDO1: U2.5 (2A), U3.23 (IO15)
/KDO2: U2.14 (3A), U3.27 (IO16)
/KDO3: U2.11 (4A), U3.28 (IO17)
/KDO4: U2.3 (1B), U3.30 (IO18)
/KDO5: U2.6 (2B), U3.31 (IO19)
/KDO6: U2.13 (3B), U3.33 (IO21)
/KDO7: U2.10 (4B), U3.36 (IO22)
/MPXi: R7.1, R21.1, U2.1 (~A/B), U3.14 (IO12)
/PS2_CLK: R12.2, U3.9 (IO33)
/PS2_DATA: R13.2, U3.8 (IO32)
/RTS: J3.5, Q1.1 (E1), R10.2
/RXD: J3.2, U3.34 (RXD0)
/TXD: J3.3, U3.35 (TXD0)
/VCC: D1.1 (K), D2.1 (K), F1.1
/VCCPG: D2.2 (A), J3.1
/~PGM: Q1.3 (C2), R14.1, U3.25 (IO0)
/~RESET: C4.1, Q1.6 (C1), R15.2, U3.3 (EN)
/~RTSNi: R1.1, R20.1, U2.15 (~G), U3.7 (IO35)
GNDPWR: C1.2, C2.2, C3.2, C4.2, D3.1 (K), J1.9, J2.3, J2.7 (GNDPWR), J3.8, SW1.1, U1.1 (GND), U2.8 (GND), U3.1 (GND), U3.15 (GND), U3.38 (GND), U3.39 (GND-PAD)
unnamed: D1.2 (A), J1.1
unnamed: D3.2 (A), R17.2
unnamed: J1.2, R1.2
unnamed: J1.3, R2.1
unnamed: J1.4, R3.1
unnamed: J1.5, R4.2
unnamed: J1.6, R5.1
unnamed: J1.7, R6.1
unnamed: J1.8, R7.2
unnamed: J2.1, R8.2, R13.1
unnamed: J2.5, JP1.2 (B), R9.2, R12.1
unnamed: J2.6, JP1.1 (A)
unnamed: Q1.2 (B1), R11.1
unnamed: Q1.5 (B2), R10.1
unnamed: R16.1, SW1.2, U3.6 (IO34)
unnamed: R17.1, U3.24 (IO2)

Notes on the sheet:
DSCK
DTR
RTS
NB: MPX must be strapped low or N/C.
Mouse Signal Key 2 - N/C (pulled high internally) 3 MSCTRL - Mouse Control Clock 4 MSDATA - Mouse Data 5 - Strap low 6 - Strap low 7 - Strap high 8 - Strap low
TXD
VCC
ESP32 Programming & UART Interface
RXD
DSCK / DSDA - I2C Interface to an OLED Display. RXD/TXD. - UART Receive and Transmit. DTR/RTS - UART control lines used for programming and reset of the ESP32. NB: MPX must be strapped low or N/C to program.
X68000 Keyboard Signal Key 2 - N/C (pulled high internally) 3 TXD - Transmit Data 4 RXD - Receive Data 5 READY - Keyboard Ready 6 REMOTE - Remote 7 - Strap low 8 - Strap low
X1 Signal Key 2 - Strap low 3 DATA - X1 Key Data 4 - Strap low 5 - Strap low 6 - Strap low 7 - Strap low 8 - Strap low
MZ-2500/2800 Signal Key 2 ~{RTSN} - H:Row Sent, L:Key Data Returned 3 KD0 - 4 KD1 - 5 KD2 - 6 KD3 - Bi-directional Bus 7 KD4 - H:Key Data, L:Strobe All Data 8 MPX - H:Upper Nibble, L:Lower Nibble
DSDA
GND

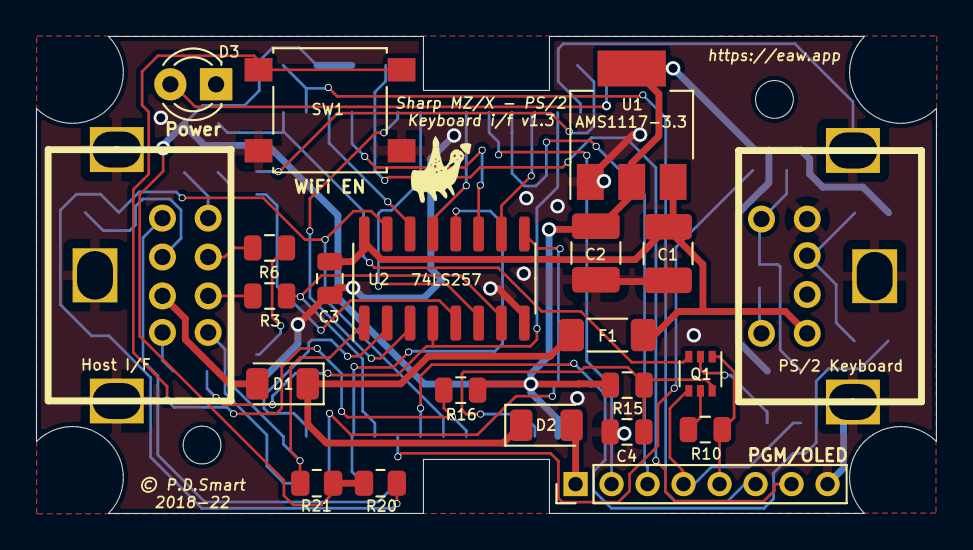
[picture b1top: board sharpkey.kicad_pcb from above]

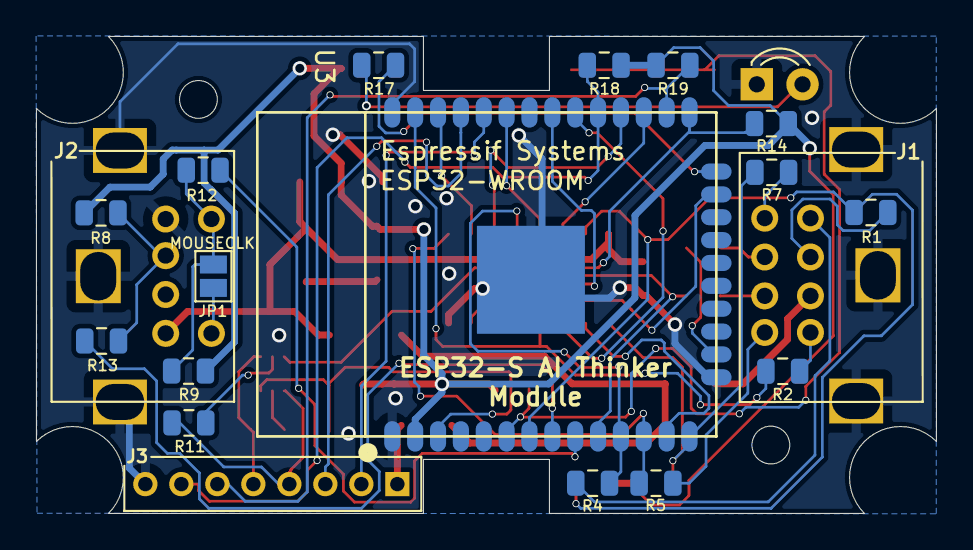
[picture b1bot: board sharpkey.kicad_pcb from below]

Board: 2 copper layers, 50.0 x 26.5 mm, 41 parts (16 on the bottom side), 46 nets.

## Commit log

2022-05-28 First release version v1.02
2022-05-28 Added docs
2022-05-28 Git displaying wrong language
2022-05-28 Added component dependency
2022-06-02 Relocated include files.
2022-06-05 Adding in MZ-5600/MZ-6500/NEC PC9801/Bluetooth modules.
2022-06-19 Added Bluetooth modules and updates
2022-06-25 Updated documents with v1.04 of User Manual and Technical Guide
2022-06-25 Build script hardcode removed
2022-06-27 Release v1.04 - Bluetooth added. MZ5665 and PC9801 are present but not tested
2022-06-27 Bug found in PS2 Mouse detection logic
2022-09-04 Added source code, MZ6500 module still not complete
2022-09-04 Schematic updates and docs
2022-09-04 Update to README
2022-09-04 Updated license file
2023-05-10 Update to host detection logic
2023-05-24 Updates to PC-9801/X68000 detection algorithm

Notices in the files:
README.md:
Licenses:
This design, hardware and software, is licensed under the GNU Public Licence v3.
No commercial use to be made of this design or any hardware/firmware component without express permission from the author. This condition overrides
any rights afforded by the GNU GPL 3 license.
The Gnu Public License v3: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
kicad/sharpkey.kicad_pcb:
© P.D.Smart
